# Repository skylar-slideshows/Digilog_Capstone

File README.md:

# Digitally Controlled Analog Mixing Console

### Capstone, 2026, Northeastern University Department of Electrical Engineering

### Contributors: Skylar Denno, Darya Petrova, Evan Forcucci, Xinhao Chen, Luke Garrity, Daniel Salas

### Advisor: [Milad Siami](https://coe.northeastern.edu/people/siami-milad/)

## [Firmware Documentation](https://docs.skylar.lgbt/)

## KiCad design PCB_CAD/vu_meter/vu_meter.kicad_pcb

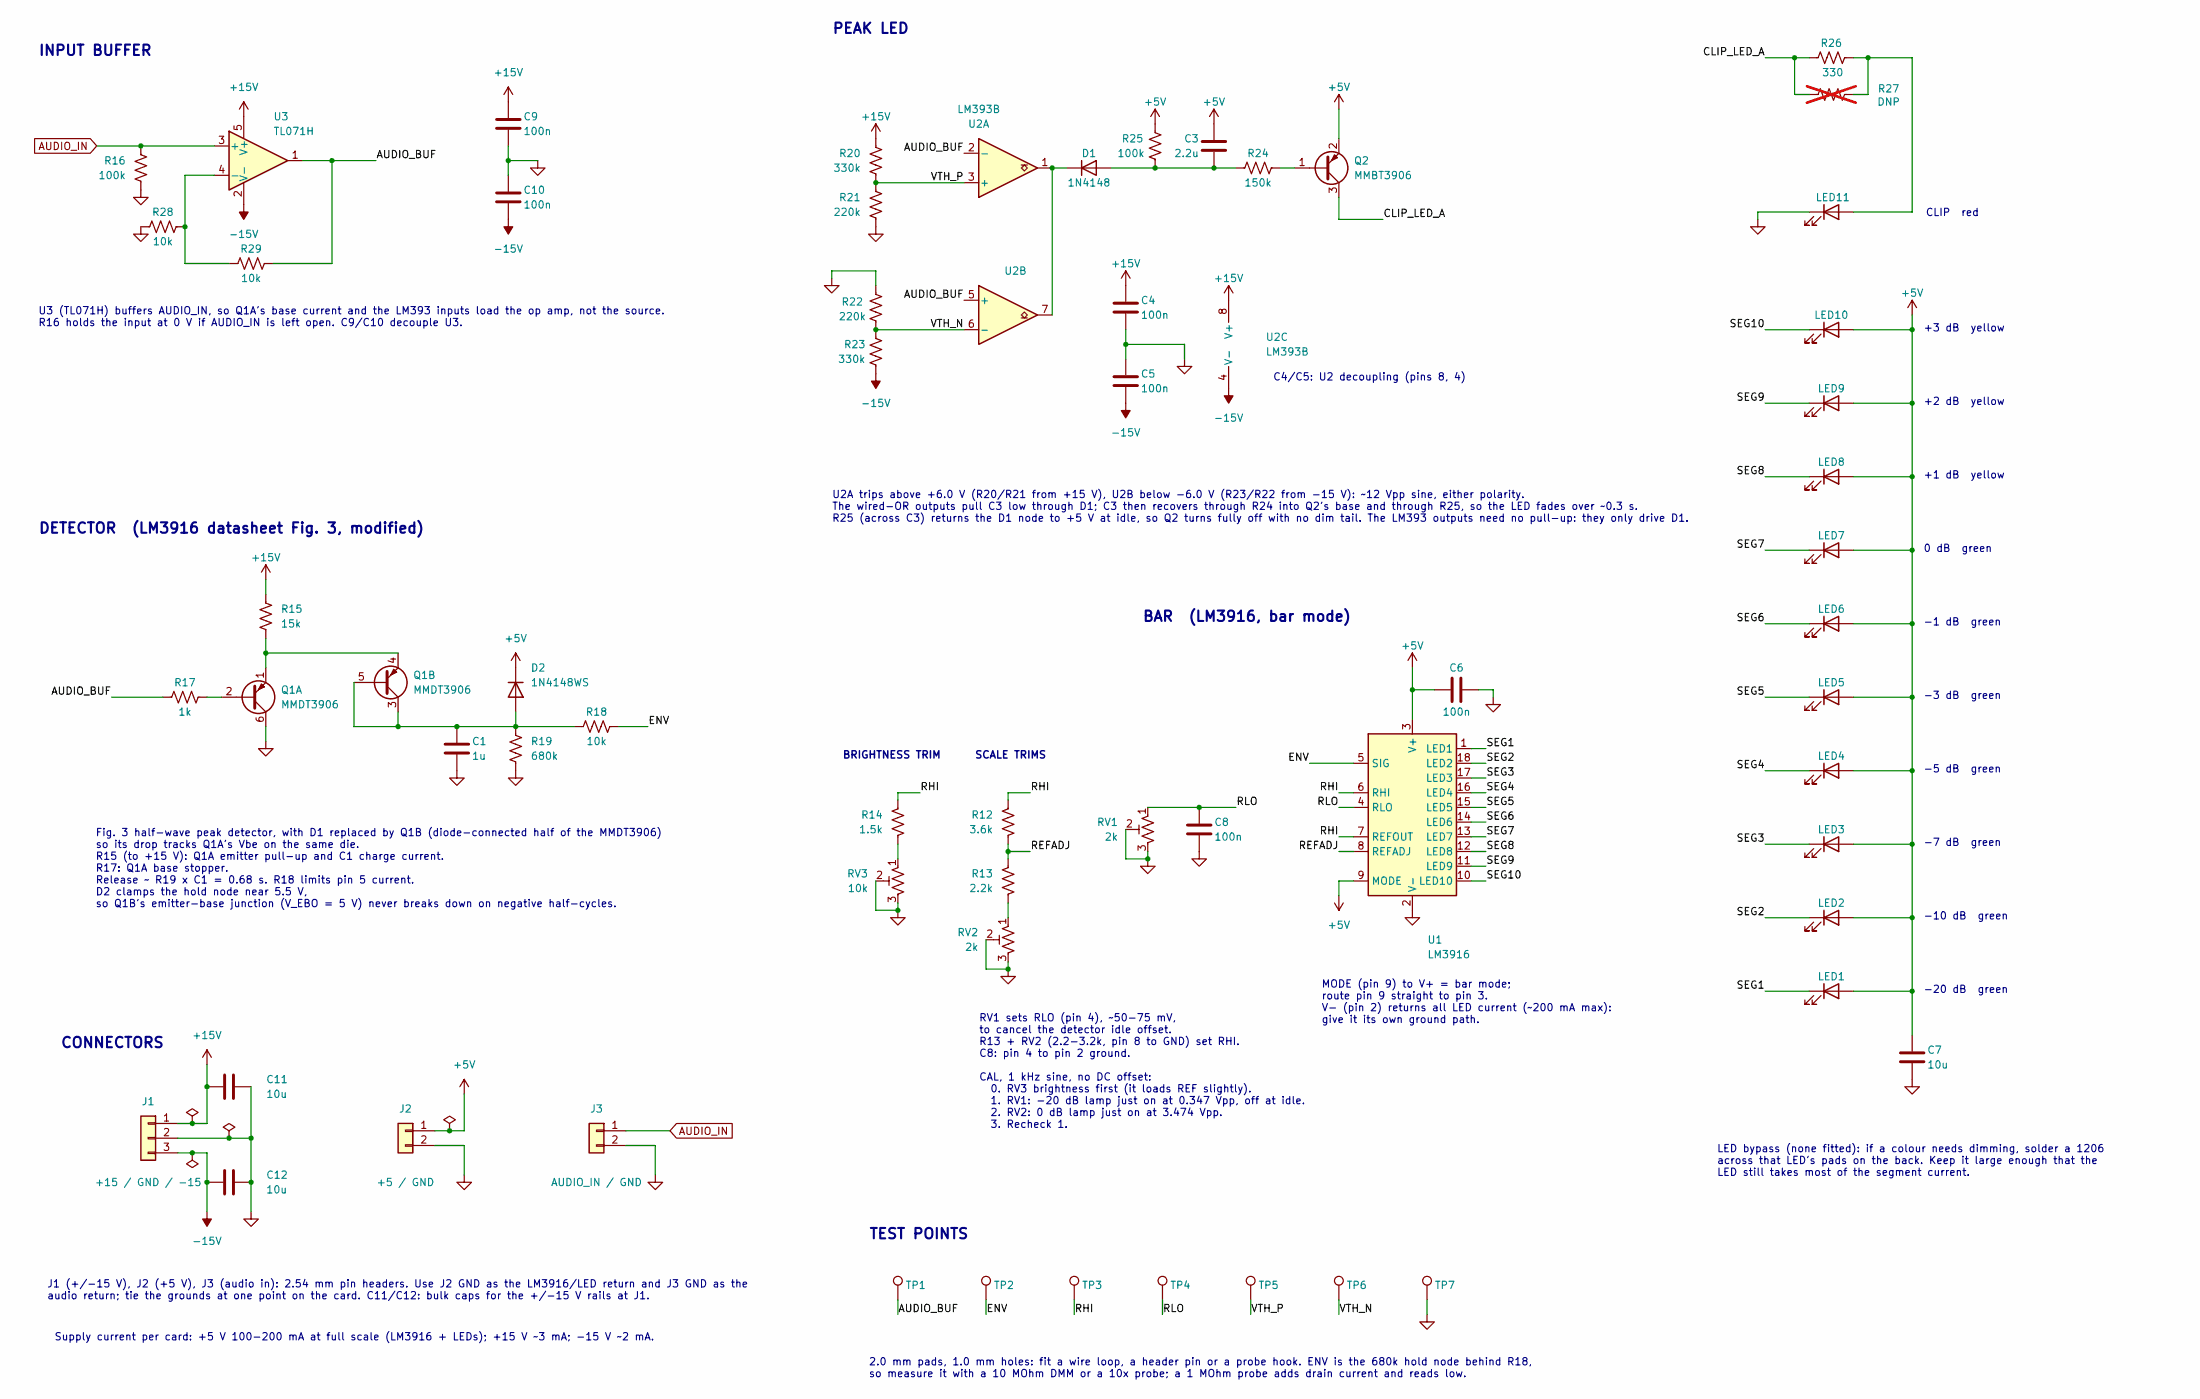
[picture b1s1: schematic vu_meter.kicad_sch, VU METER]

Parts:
C1: 1u; C_0805_2012Metric; MPN Samsung CL21B105KBFNNNE; LCSC C28323
C3: 2.2u; C_1206_3216Metric; MPN Samsung CL31B225KBHNNNE; LCSC C50254
C4, C5, C6, C8, C9, C10: 100n; C_0603_1608Metric; LCSC C1591
C7, C11, C12: 10u; C_1206_3216Metric; MPN Samsung CL31A106KBHNNNE; LCSC C13585
D1: 1N4148; D_SOD-323; LCSC C2128
D2: 1N4148WS; D_SOD-323; MPN JSCJ 1N4148WS; LCSC C2128
J1: +15 / GND / -15; PinHeader_1x03_P2.54mm_Vertical; LCSC DNP
J2: +5 / GND; PinHeader_1x02_P2.54mm_Vertical; LCSC DNP
J3: AUDIO_IN / GND; PinHeader_1x02_P2.54mm_Vertical; LCSC DNP
LED1, LED2, LED3, LED4, LED5, LED6, LED7: LED green; LED_Rectangular_W5.0mm_H2.0mm; LCSC DNP
LED8, LED9, LED10: LED yellow; LED_Rectangular_W5.0mm_H2.0mm; LCSC DNP
LED11: PEAK red; LED_Rectangular_W5.0mm_H2.0mm; LCSC DNP
Q1: MMDT3906; SOT-363_SC-70-6; LCSC C508227
Q2: MMBT3906; SOT-23; LCSC C82762
R12: 3.6k; R_0603_1608Metric; MPN UNI-ROYAL 0603WAF3601T5E; LCSC C22980
R13: 2.2k; R_0603_1608Metric; MPN UNI-ROYAL 0603WAF2201T5E; LCSC C4190
R14: 1.5k; R_0603_1608Metric; MPN UNI-ROYAL 0603WAF1501T5E; LCSC C22843
R15: 15k; R_0603_1608Metric; MPN UNI-ROYAL 0603WAF1502T5E; LCSC C22809
R16, R25: 100k; R_0603_1608Metric; MPN UNI-ROYAL 0603WAF1003T5E; LCSC C25803
R17: 1k; R_0603_1608Metric; MPN UNI-ROYAL 0603WAF1001T5E; LCSC C21190
R18, R28, R29: 10k; R_0603_1608Metric; MPN UNI-ROYAL 0603WAF1002T5E; LCSC C25804
R19: 680k; R_0603_1608Metric; MPN UNI-ROYAL 0603WAF6803T5E; LCSC C25822
R20, R23: 330k; R_0603_1608Metric; MPN UNI-ROYAL 0603WAF3303T5E; LCSC C23137
R21, R22: 220k; R_0603_1608Metric; MPN UNI-ROYAL 0603WAF2203T5E; LCSC C22961
R24: 150k; R_0603_1608Metric; MPN UNI-ROYAL 0603WAF1503T5E; LCSC C22807
R26: 330; R_0603_1608Metric; MPN UNI-ROYAL 0603WAF3300T5E; LCSC C23138
R27: DNP; R_Axial_DIN0207_L6.3mm_D2.5mm_P7.62mm_Horizontal; LCSC DNP; not fitted
RV1, RV2: 2k; Potentiometer_Bourns_3006P_Horizontal; LCSC DNP
RV3: 10k; Potentiometer_Bourns_3006P_Horizontal; LCSC DNP
TP1: AUDIO_BUF; TestPoint_THTPad_D2.0mm_Drill1.0mm; LCSC DNP
TP2: ENV; TestPoint_THTPad_D2.0mm_Drill1.0mm; LCSC DNP
TP3: RHI; TestPoint_THTPad_D2.0mm_Drill1.0mm; LCSC DNP
TP4: RLO; TestPoint_THTPad_D2.0mm_Drill1.0mm; LCSC DNP
TP5: VTH_P; TestPoint_THTPad_D2.0mm_Drill1.0mm; LCSC DNP
TP6: VTH_N; TestPoint_THTPad_D2.0mm_Drill1.0mm; LCSC DNP
TP7: GND; TestPoint_THTPad_D2.0mm_Drill1.0mm; LCSC DNP
U1: LM3916; DIP-18_W7.62mm_Socket; LCSC DNP
U2: LM393B; SOIC-8_3.9x4.9mm_P1.27mm; LCSC C2865059
U3: TL071H; SOT-23-5; MPN TI TL071HIDBVR; LCSC C4370629

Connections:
+5V: C3.1, C6.1, C7.1, D2.1 (K), J2.1, LED1.2 (A), LED2.2 (A), LED3.2 (A), LED4.2 (A), LED5.2 (A), LED6.2 (A), LED7.2 (A), LED8.2 (A), LED9.2 (A), LED10.2 (A), Q2.2 (E), R25.1, U1.3 (V+), U1.9 (MODE)
+15V: C4.1, C9.1, C11.1, J1.1, R15.1, R20.1, U2.8 (V+), U3.5 (V+)
-15V: C5.2, C10.2, C12.1, J1.3, R23.2, U2.4 (V-), U3.2 (V-)
/AUDIO_BUF: R17.1, R29.2, TP1.1 (1_1), U2.2 (-), U2.5 (+), U3.1
/CLIP_LED_A: Q2.3 (C), R26.1, R27.1
/ENV: R18.2, TP2.1 (1_1), U1.5 (SIG)
/REFADJ: R12.2, R13.1, U1.8 (REFADJ)
/RHI: R12.1, R14.1, TP3.1 (1_1), U1.6 (RHI), U1.7 (REFOUT)
/RLO: C8.1, RV1.1, TP4.1 (1_1), U1.4 (RLO)
/SEG1: LED1.1 (K), U1.1 (LED1)
/SEG2: LED2.1 (K), U1.18 (LED2)
/SEG3: LED3.1 (K), U1.17 (LED3)
/SEG4: LED4.1 (K), U1.16 (LED4)
/SEG5: LED5.1 (K), U1.15 (LED5)
/SEG6: LED6.1 (K), U1.14 (LED6)
/SEG7: LED7.1 (K), U1.13 (LED7)
/SEG8: LED8.1 (K), U1.12 (LED8)
/SEG9: LED9.1 (K), U1.11 (LED9)
/SEG10: LED10.1 (K), U1.10 (LED10)
/VTH_N: R22.2, R23.1, TP6.1 (1_1), U2.6 (-)
/VTH_P: R20.2, R21.1, TP5.1 (1_1), U2.3 (+)
AUDIO_IN: J3.1, R16.1, U3.3 (+)
GND: C1.2, C4.2, C5.1, C6.2, C7.2, C8.2, C9.2, C10.1, C11.2, C12.2, J1.2, J2.2, J3.2, LED11.1 (K), Q1.6 (C1), R16.2, R19.2, R21.2, R22.1, R28.1, RV1.2, RV1.3, RV2.2, RV2.3, RV3.2, RV3.3, TP7.1 (1_1), U1.2 (V-)
unnamed: C3.2, D1.2 (A), R24.1, R25.2
unnamed: D1.1 (K), U2.1, U2.7
unnamed: C1.1, D2.2 (A), Q1.3 (C2), Q1.5 (B2), R18.1, R19.1
unnamed: LED11.2 (A), R26.2, R27.2
unnamed: Q1.2 (B1), R17.2
unnamed: Q1.1 (E1), Q1.4 (E2), R15.2
unnamed: Q2.1 (B), R24.2
unnamed: R13.2, RV2.1
unnamed: R14.2, RV3.1
unnamed: R28.2, R29.1, U3.4 (-)

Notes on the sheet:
SCALE TRIMS
INPUT BUFFER
LED bypass (none fitted): if a colour needs dimming, solder a 1206 across that LED's pads on the back. Keep it large enough that the LED still takes most of the segment current.
J1 (+/-15 V), J2 (+5 V), J3 (audio in): 2.54 mm pin headers. Use J2 GND as the LM3916/LED return and J3 GND as the audio return; tie the grounds at one point on the card. C11/C12: bulk caps for the +/-15 V rails at J1.
Supply current per card: +5 V 100-200 mA at full scale (LM3916 + LEDs); +15 V ~3 mA; -15 V ~2 mA.
Fig. 3 half-wave peak detector, with D1 replaced by Q1B (diode-connected half of the MMDT3906) so its drop tracks Q1A's Vbe on the same die. R15 (to +15 V): Q1A emitter pull-up and C1 charge current. R17: Q1A base stopper. Release ~ R19 x C1 = 0.68 s. R18 limits pin 5 current. D2 clamps the hold no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
MODE (pin 9) to V+ = bar mode; route pin 9 straight to pin 3. V- (pin 2) returns all LED current (~200 mA max): give it its own ground path.
-20 dB green
-10 dB green
-7 dB green
-5 dB green
-3 dB green
-1 dB green
0 dB green
+1 dB yellow
+2 dB yellow
+3 dB yellow
BAR (LM3916, bar mode)
RV1 sets RLO (pin 4), ~50-75 mV, to cancel the detector idle offset. R13 + RV2 (2.2-3.2k, pin 8 to GND) set RHI. C8: pin 4 to pin 2 ground. CAL, 1 kHz sine, no DC offset: 0. RV3 brightness first (it loads REF slightly). 1. RV1: -20 dB lamp just on at 0.347 Vpp, off at idle. 2. RV2: 0 dB lamp just o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
C4/C5: U2 decoupling (pins 8, 4)
DETECTOR (LM3916 datasheet Fig. 3, modified)
PEAK LED
U2A trips above +6.0 V (R20/R21 from +15 V), U2B below -6.0 V (R23/R22 from -15 V): ~12 Vpp sine, either polarity. The wired-OR outputs pull C3 low through D1; C3 then recovers through R24 into Q2's base and through R25, so the LED fades over ~0.3 s. R25 (across C3) returns the D1 node to +5 V at i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
U3 (TL071H) buffers AUDIO_IN, so Q1A's base current and the LM393 inputs load the op amp, not the source. R16 holds the input at 0 V if AUDIO_IN is left open. C9/C10 decouple U3.
CLIP red
TEST POINTS
CONNECTORS
2.0 mm pads, 1.0 mm holes: fit a wire loop, a header pin or a probe hook. ENV is the 680k hold node behind R18, so measure it with a 10 MOhm DMM or a 10x probe; a 1 MOhm probe adds drain current and reads low.
BRIGHTNESS TRIM

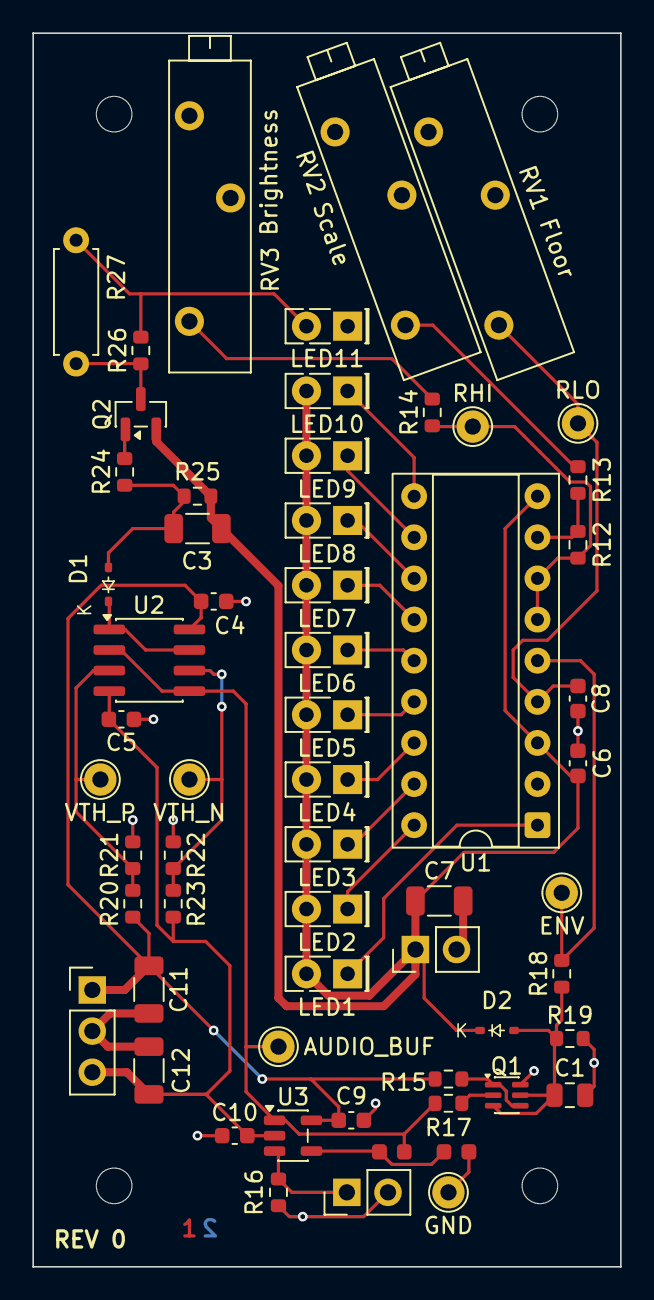
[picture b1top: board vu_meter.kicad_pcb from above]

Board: 2 copper layers, 36.3 x 76.2 mm, 64 parts (0 on the bottom side), 33 nets.

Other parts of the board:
H1, H2, H3, H4: MountingHole_2.2mm_M2

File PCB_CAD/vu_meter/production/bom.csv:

Designator,Footprint,Quantity,Value,LCSC Part #
C1,0805,1,1u,C28323
"C10, C4, C5, C6, C8, C9",0603,6,100n,C1591
"C11, C12, C7",1206,3,10u,C13585
C3,1206,1,2.2u,C50254
D1,D_SOD-323,1,1N4148,C2128
D2,D_SOD-323,1,1N4148WS,C2128
J1,PinHeader_1x03_P2.54mm_Vertical,1,+15 / GND / -15,DNP
J2,PinHeader_1x02_P2.54mm_Vertical,1,+5 / GND,DNP
J3,PinHeader_1x02_P2.54mm_Vertical,1,AUDIO_IN / GND,DNP
"LED1, LED2, LED3, LED4, LED5, LED6, LED7",LED_Rectangular_W5.0mm_H2.0mm,7,LED green,DNP
"LED10, LED8, LED9",LED_Rectangular_W5.0mm_H2.0mm,3,LED yellow,DNP
LED11,LED_Rectangular_W5.0mm_H2.0mm,1,PEAK red,DNP
Q1,SOT-363_SC-70-6,1,MMDT3906,C508227
Q2,SOT-23,1,MMBT3906,C82762
R12,0603,1,3.6k,C22980
R13,0603,1,2.2k,C4190
R14,0603,1,1.5k,C22843
R15,0603,1,15k,C22809
"R16, R25",0603,2,100k,C25803
R17,0603,1,1k,C21190
"R18, R28, R29",0603,3,10k,C25804
R19,0603,1,680k,C25822
"R20, R23",0603,2,330k,C23137
"R21, R22",0603,2,220k,C22961
R24,0603,1,150k,C22807
R26,0603,1,330,C23138
"RV1, RV2",Potentiometer_Bourns_3006P_Horizontal,2,2k,DNP
RV3,Potentiometer_Bourns_3006P_Horizontal,1,10k,DNP
U1,DIP-18_W7.62mm_Socket,1,LM3916,DNP
U2,SOIC-8_3.9x4.9mm_P1.27mm,1,LM393B,C2865059
U3,SOT-23-5,1,TL071H,C4370629

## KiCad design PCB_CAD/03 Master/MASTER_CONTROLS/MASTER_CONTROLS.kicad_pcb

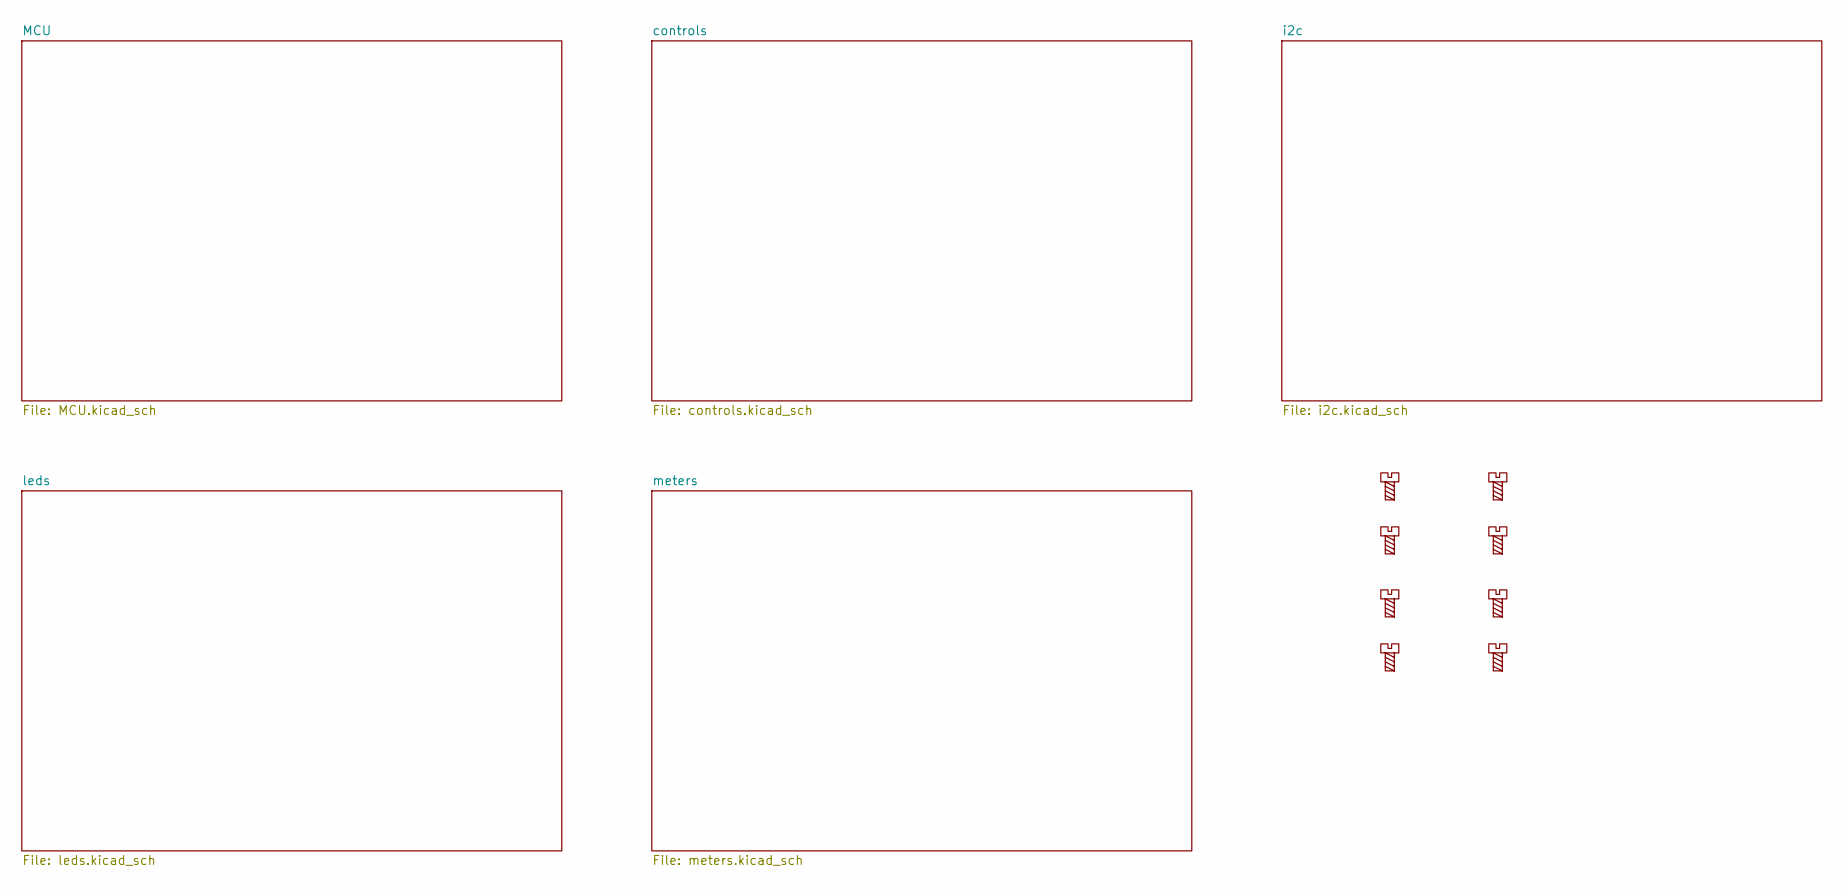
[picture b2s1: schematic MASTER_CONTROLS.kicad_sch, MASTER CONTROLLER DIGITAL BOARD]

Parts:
H1, H2, H3, H4, H5, H6, H7, H8: MountingScrew; MountingHole_3.2mm_M3; LCSC dnp

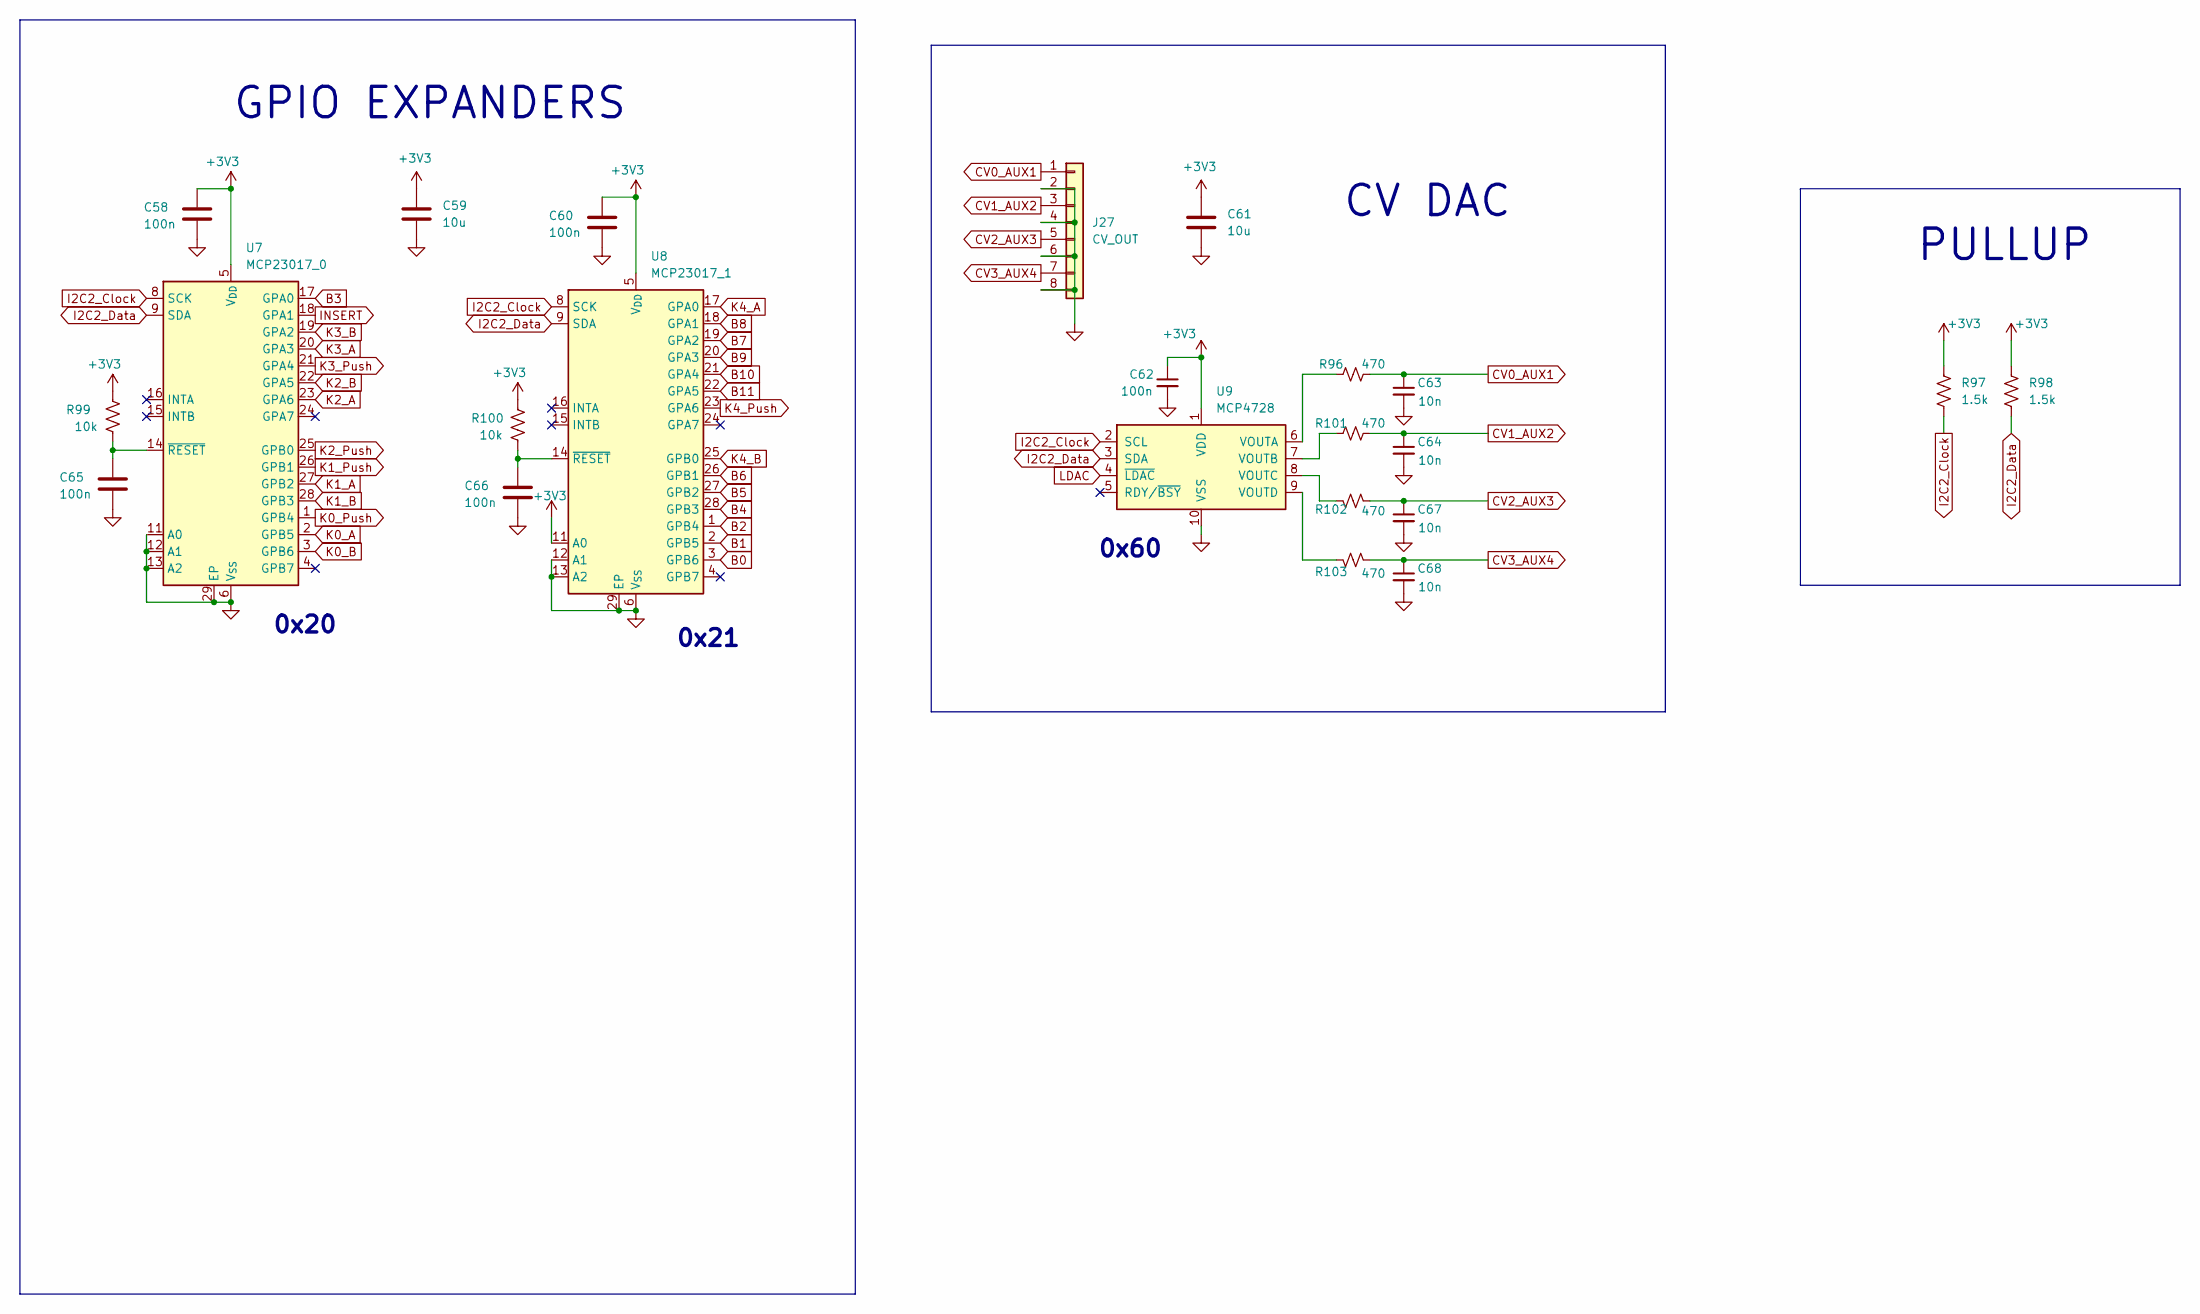
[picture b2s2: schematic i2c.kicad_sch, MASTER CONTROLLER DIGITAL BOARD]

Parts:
C58, C60, C62, C65, C66: 100n; C_0603_1608Metric; LCSC C1590
C59, C61: 10u; C_1206_3216Metric; LCSC C1849
C63, C64, C67, C68: 10n; C_0402_1005Metric; LCSC C1524
J27: CV_OUT; PinHeader_1x08_P2.54mm_Vertical; LCSC DNP
R96, R101, R102, R103: 470; R_0603_1608Metric; LCSC C23179
R97, R98: 1.5k; R_0603_1608Metric; LCSC C22843
R99, R100: 10k; R_0603_1608Metric; LCSC C25804
U7: MCP23017_0; QFN-28-1EP_6x6mm_P0.65mm_EP4.25x4.25mm; LCSC C629439
U8: MCP23017_1; QFN-28-1EP_6x6mm_P0.65mm_EP4.25x4.25mm; LCSC C629439
U9: MCP4728; MSOP-10_3x3mm_P0.5mm; LCSC C108207

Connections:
+3V3: C58.1, C59.1, C60.1, C61.1, C62.1, R97.1, R98.1, R99.1, R100.1, U7.5 (V_{DD}), U8.5 (V_{DD}), U8.11 (A0), U9.1 (VDD); also elsewhere on the board
B0: U8.3 (GPB6); also elsewhere on the board
B1: U8.2 (GPB5); also elsewhere on the board
B2: U8.1 (GPB4); also elsewhere on the board
B3: U7.17 (GPA0); also elsewhere on the board
B4: U8.28 (GPB3); also elsewhere on the board
B5: U8.27 (GPB2); also elsewhere on the board
B6: U8.26 (GPB1); also elsewhere on the board
B7: U8.19 (GPA2); also elsewhere on the board
B8: U8.18 (GPA1); also elsewhere on the board
B9: U8.20 (GPA3); also elsewhere on the board
B10: U8.21 (GPA4); also elsewhere on the board
B11: U8.22 (GPA5); also elsewhere on the board
CV0_AUX1: C63.1, J27.1, R96.2
CV1_AUX2: C64.1, J27.3, R101.2
CV2_AUX3: C67.1, J27.5, R102.2
CV3_AUX4: C68.1, J27.7, R103.2
GND: C58.2, C59.2, C60.2, C61.2, C62.2, C63.2, C64.2, C65.2, C66.2, C67.2, C68.2, J27.2, J27.4, J27.6, J27.8, U7.6 (V_{SS}), U7.11 (A0), U7.12 (A1), U7.13 (A2), U7.29 (EP), U8.6 (V_{SS}), U8.12 (A1), U8.13 (A2), U8.29 (EP), U9.10 (VSS); also elsewhere on the board
I2C2_Clock: R97.2, U7.8 (SCK), U8.8 (SCK), U9.2 (SCL); also elsewhere on the board
I2C2_Data: R98.2, U7.9 (SDA), U8.9 (SDA), U9.3 (SDA); also elsewhere on the board
INSERT: U7.18 (GPA1); also elsewhere on the board
K0_A: U7.2 (GPB5); also elsewhere on the board
K0_B: U7.3 (GPB6); also elsewhere on the board
K0_Push: U7.1 (GPB4); also elsewhere on the board
K1_A: U7.27 (GPB2); also elsewhere on the board
K1_B: U7.28 (GPB3); also elsewhere on the board
K1_Push: U7.26 (GPB1); also elsewhere on the board
K2_A: U7.23 (GPA6); also elsewhere on the board
K2_B: U7.22 (GPA5); also elsewhere on the board
K2_Push: U7.25 (GPB0); also elsewhere on the board
K3_A: U7.20 (GPA3); also elsewhere on the board
K3_B: U7.19 (GPA2); also elsewhere on the board
K3_Push: U7.21 (GPA4); also elsewhere on the board
K4_A: U8.17 (GPA0); also elsewhere on the board
K4_B: U8.25 (GPB0); also elsewhere on the board
K4_Push: U8.23 (GPA6); also elsewhere on the board
LDAC: U9.4 (~LDAC); also elsewhere on the board
unnamed: C65.1, R99.2, U7.14 (~RESET)
unnamed: C66.1, R100.2, U8.14 (~RESET)
unnamed: R96.1, U9.6 (VOUTA)
unnamed: R101.1, U9.7 (VOUTB)
unnamed: R102.1, U9.8 (VOUTC)
unnamed: R103.1, U9.9 (VOUTD)

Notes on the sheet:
0x20
CV DAC
GPIO EXPANDERS
0x60
0x21
PULLUP

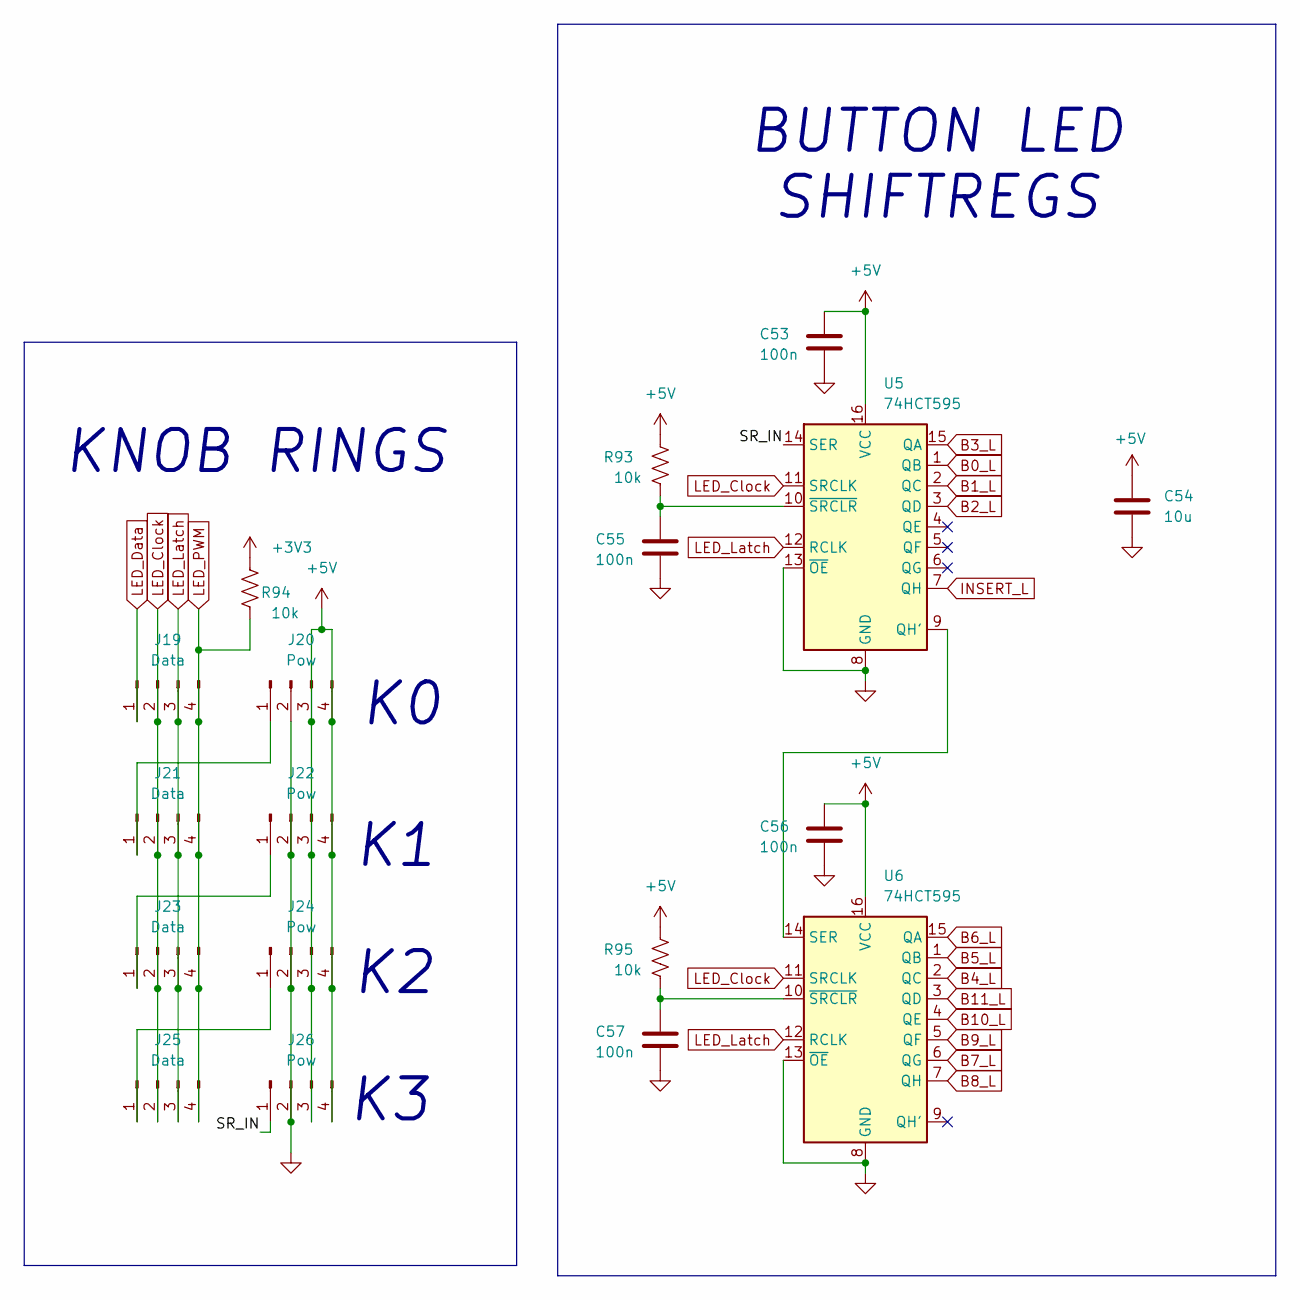
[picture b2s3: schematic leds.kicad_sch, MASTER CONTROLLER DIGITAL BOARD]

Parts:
C53, C55, C56, C57: 100n; C_0603_1608Metric; LCSC C1590
C54: 10u; C_1206_3216Metric; LCSC C1849
J19, J21, J23, J25: Data; PinSocket_1x04_P2.54mm_Vertical; LCSC DNP
J20, J22, J24, J26: Pow; PinSocket_1x04_P2.54mm_Vertical; LCSC DNP
R93, R94, R95: 10k; R_0603_1608Metric; LCSC C25804
U5, U6: 74HCT595; SOIC-16_3.9x9.9mm_P1.27mm; LCSC C282339

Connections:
+3V3: R94.1; also elsewhere on the board
+5V: C53.1, C54.1, C56.1, J20.3, J20.4, J22.3, J22.4, J24.3, J24.4, J26.3, J26.4, R93.1, R95.1, U5.16 (VCC), U6.16 (VCC); also elsewhere on the board
/leds/SR_IN: J26.1, U5.14 (SER)
B0_L: U5.1 (QB); also elsewhere on the board
B1_L: U5.2 (QC); also elsewhere on the board
B2_L: U5.3 (QD); also elsewhere on the board
B3_L: U5.15 (QA); also elsewhere on the board
B4_L: U6.2 (QC); also elsewhere on the board
B5_L: U6.1 (QB); also elsewhere on the board
B6_L: U6.15 (QA); also elsewhere on the board
B7_L: U6.6 (QG); also elsewhere on the board
B8_L: U6.7 (QH); also elsewhere on the board
B9_L: U6.5 (QF); also elsewhere on the board
B10_L: U6.4 (QE); also elsewhere on the board
B11_L: U6.3 (QD); also elsewhere on the board
GND: C53.2, C54.2, C55.2, C56.2, C57.2, J20.2, J22.2, J24.2, J26.2, U5.8 (GND), U5.13 (~OE), U6.8 (GND), U6.13 (~OE); also elsewhere on the board
INSERT_L: U5.7 (QH); also elsewhere on the board
LED_Clock: J19.2, J21.2, J23.2, J25.2, U5.11 (SRCLK), U6.11 (SRCLK); also elsewhere on the board
LED_Data: J19.1; also elsewhere on the board
LED_Latch: J19.3, J21.3, J23.3, J25.3, U5.12 (RCLK), U6.12 (RCLK); also elsewhere on the board
LED_PWM: J19.4, J21.4, J23.4, J25.4, R94.2; also elsewhere on the board
unnamed: J20.1, J21.1
unnamed: J22.1, J23.1
unnamed: J24.1, J25.1
unnamed: U5.9 (QH'), U6.14 (SER)
unnamed: C55.1, R93.2, U5.10 (~SRCLR)
unnamed: C57.1, R95.2, U6.10 (~SRCLR)

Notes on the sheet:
BUTTON LED SHIFTREGS
KNOB RINGS
